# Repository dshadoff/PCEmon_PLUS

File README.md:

# PCEmon_PLUS

This project is meant to enhance Chris Covell's PCEmon, which can be found here:
https://chrismcovell.com/PCEmon/index.html

This board implements a microcontroller (Adafruit Feather M0 Adalogger), to
simplify some operations and to generally make life easier for the PCEmon user.
Software is written using the Arduino IDE.

I am hoping that others find this useful, and are able to contribute to the
project in order to add new functionality.  I am open to improving the hardware
in future, if it would be helpful for the functionality added.

Features:
- Instead of swapping cables between joypad and computer, this board can change
which input is active, with the touch of a pad on the microcontroller board
- Currently, it powers up with a shell pass-thru interface with the original
PCEmon commands; touching the 'PLUS mode' touchpad on the board will bring up
an alternate interface which is being built, but can currently view and scroll
through main memory and VRAM (with more to come)

NOTES:
------
Recommended Teraterm settings by Setup menu area:
Terminal:
- New-line: Transmit - change to LF

Font:
- If you use Teraterm on Windows, I found that the default font is thin and wispy; a better
  font to use is "HGSoeiKakuGothicUB" (Regular)

Serial Port:
- Start with default 19200

Additional Settings, 'General' tab:
- Unset "Clear display when window resized"
- Set "Display serial port speed"

TODOs:
------
- Add interactive memory edit
- Add ZMODEM transfers for easier data handling
- Add disassembler (and save to SDCard/computer)
- Add more clever management of input control (i.e. PCE can signal back with
extended /CLR=high signal, that PCE is ready for PCEmoninput)

This is prototype software, and as such has been minimally tested.
Use at your own risk.

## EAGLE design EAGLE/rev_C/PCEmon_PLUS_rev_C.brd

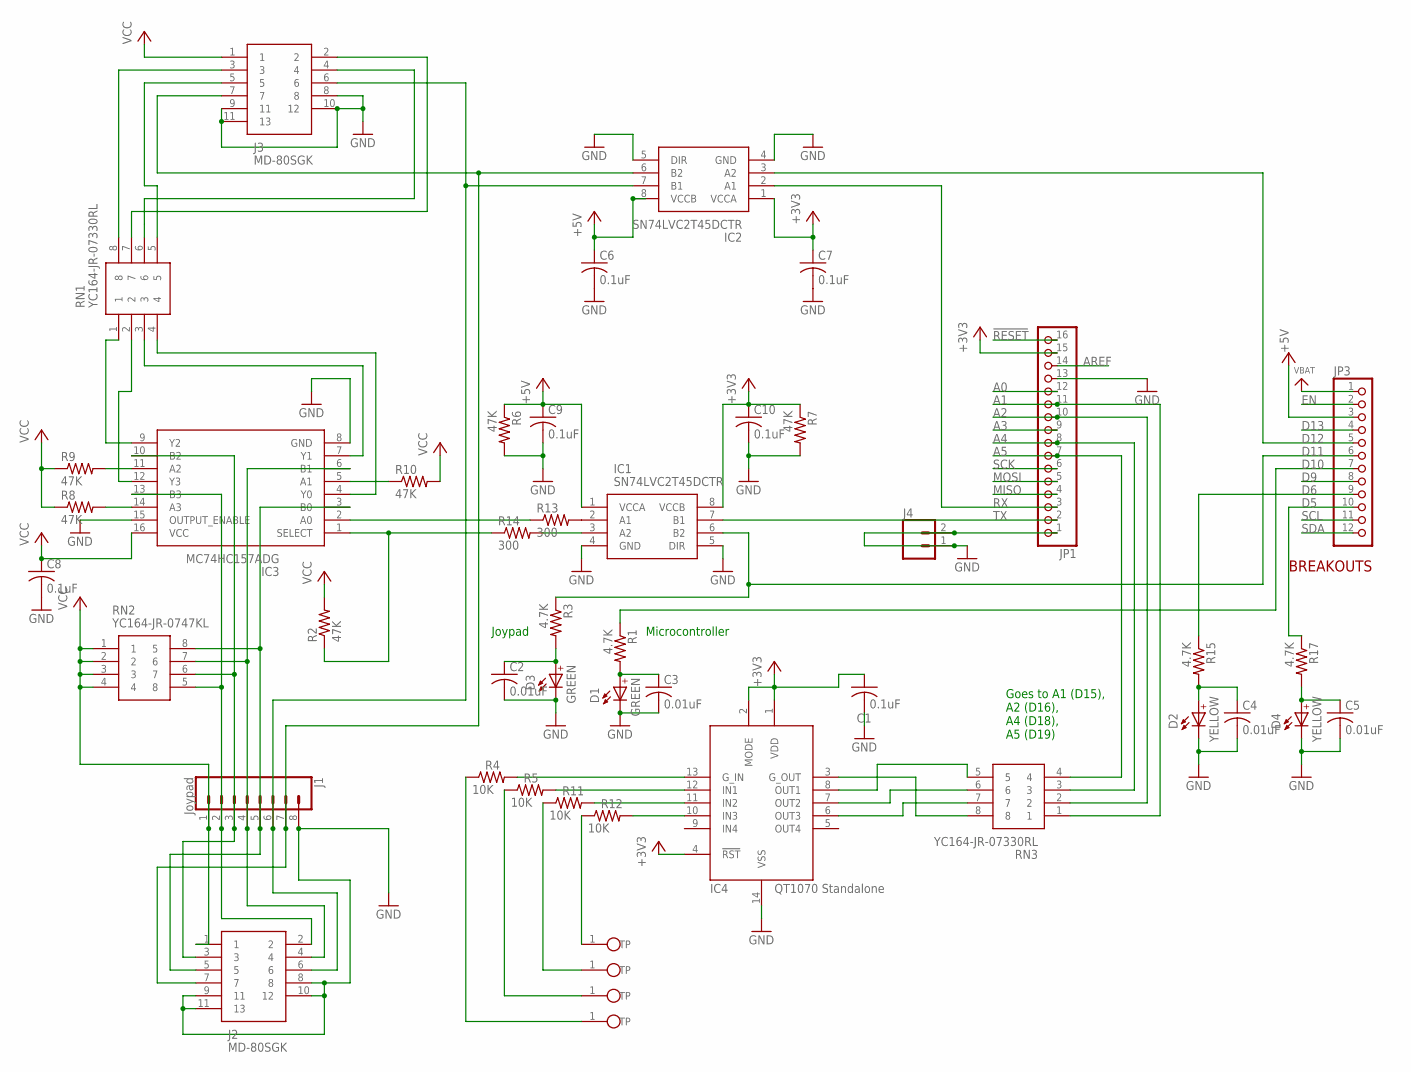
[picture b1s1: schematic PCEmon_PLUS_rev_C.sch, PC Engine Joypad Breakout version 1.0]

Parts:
C1, C6, C7, C8, C9, C10: 0.1uF; C0603
C2, C3, C4, C5: 0.01uF; C0603
D1, D3: GREEN; WL-SMCC_0603_R/Y/V
D2, D4: YELLOW; WL-SMCC_0603_R/Y/V
IC1, IC2: SN74LVC2T45DCTR; SOP65P400X130-8N
IC3: MC74HC157ADG; SOIC127P600X175-16N
IC4: AT42QT1070-SSU; SO14
J1: Joypad; 1X08
J2, J3: MD-80SGK; MD80SGK
J4: CONN_021X02_NO_SILK; 1X02_NO_SILK
JP1: HEADER-1X16ROUND; 1X16_ROUND
JP3: HEADER-1X12; 1X12_ROUND
P1: JOYPAD; TOUCH-350X500
P2: COMPUTER; TOUCH-350X500
P3: Original Mode; TOUCH-350X500
P4: PLUS Mode; TOUCH-350X500
R1, R3, R15, R17: 4.7K; R0603
R2, R6, R7, R8, R9, R10: 47K; R0603
R4, R5, R11, R12: 10K; R0603
R13, R14: 300; R0603
RN1, RN3: YC164-JR-07330RL; YC164JR07220RL
RN2: YC164-JR-0747KL; YC164JR07220RL

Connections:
!RESET: JP1.16
+3V3: C1.1, C7.1, C10.1, IC1.8 (VCCB), IC2.1 (VCCA), IC4.1 (VDD), IC4.2 (MODE), IC4.4 (!RST), JP1.15, R7.1
+5V: C6.1, C9.1, IC1.1 (VCCA), IC2.8 (VCCB), JP3.3, R6.1
A0: JP1.12
A1: JP1.11, RN3.1
A2: JP1.10, RN3.2
A3: JP1.9
A4: JP1.8, RN3.3
A5: JP1.7, RN3.4
AREF: JP1.14
D5: JP3.10, R17.1
D6: JP3.9, R15.1
D9: JP3.8
D10: JP3.7, R1.1
D11: IC1.6 (B2), JP3.6, R3.1
D12: IC2.3 (A2), JP3.5
D13: JP3.4
EN: JP3.2
GND: C1.2, C2.2, C3.2, C4.2, C5.2, C6.2, C7.2, C8.2, C9.2, C10.2, D1.1 (C), D2.1 (C), D3.1 (C), D4.1 (C), IC1.4 (GND), IC1.5 (DIR), IC2.4 (GND), IC2.5 (DIR), IC3.8 (GND), IC3.15 (OUTPUT_ENABLE), IC4.14 (VSS), J1.8, J2.8, J2.9 (11), J2.10 (12), J2.11 (13), J3.8, J3.9 (11), J3.10 (12), J3.11 (13), J4.1, J4.2, JP1.1, JP1.13, R6.2, R7.2
MISO: JP1.4
MOSI: JP1.5
unnamed: C2.1, D3.2 (A), R3.2
unnamed: IC3.10 (B2), J1.3, J2.3, RN2.6 (7)
unnamed: IC3.13 (B3), J1.2, J2.2, RN2.5 (8)
unnamed: IC3.6 (B1), J1.4, J2.4, RN2.7 (6)
unnamed: IC3.3 (B0), J1.5, J2.5, RN2.8 (5)
unnamed: IC2.7 (B1), J1.6, J2.6, J3.6
unnamed: IC2.6 (B2), J1.7, J2.7, J3.7
unnamed: J3.5, RN1.5
unnamed: C3.1, D1.2 (A), R1.2
unnamed: J3.4, RN1.6
unnamed: J3.3, RN1.8
unnamed: IC3.14 (A3), R8.2
unnamed: IC3.11 (A2), R9.2
unnamed: IC3.1 (SELECT), R2.1, R14.1
unnamed: IC1.2 (A1), R13.2
unnamed: IC3.5 (A1), R10.1
unnamed: IC3.9 (Y2), RN1.1
unnamed: IC3.2 (A0), R13.1
unnamed: IC1.3 (A2), R14.2
unnamed: IC3.12 (Y3), RN1.2
unnamed: IC4.13 (G_IN), R4.2
unnamed: IC3.4 (Y0), RN1.4
unnamed: J3.2, RN1.7
unnamed: IC3.7 (Y1), RN1.3
unnamed: IC4.12 (IN1), R5.2
unnamed: IC4.11 (IN2), R11.2
unnamed: IC4.10 (IN3), R12.2
unnamed: IC4.3 (G_OUT), RN3.8
unnamed: IC4.6 (OUT3), RN3.7
unnamed: IC4.7 (OUT2), RN3.6
unnamed: IC4.8 (OUT1), RN3.5
unnamed: P3.1, R5.1
unnamed: P4.1, R4.1
unnamed: P2.1, R11.1
unnamed: P1.1, R12.1
unnamed: C4.1, D2.2 (A), R15.2
unnamed: C5.1, D4.2 (A), R17.2
RX: IC2.2 (A1), JP1.3
SCK: JP1.6
SCL: JP3.11
SDA: JP3.12
TX: IC1.7 (B1), JP1.2
VBAT: JP3.1
VCC: C8.1, IC3.16 (VCC), J1.1, J2.1, J3.1, R2.2, R8.1, R9.1, R10.2, RN2.1, RN2.2, RN2.3, RN2.4

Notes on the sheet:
BREAKOUTS
Joypad
Microcontroller
Goes to A1 (D15), A2 (D16), A4 (D18), A5 (D19)

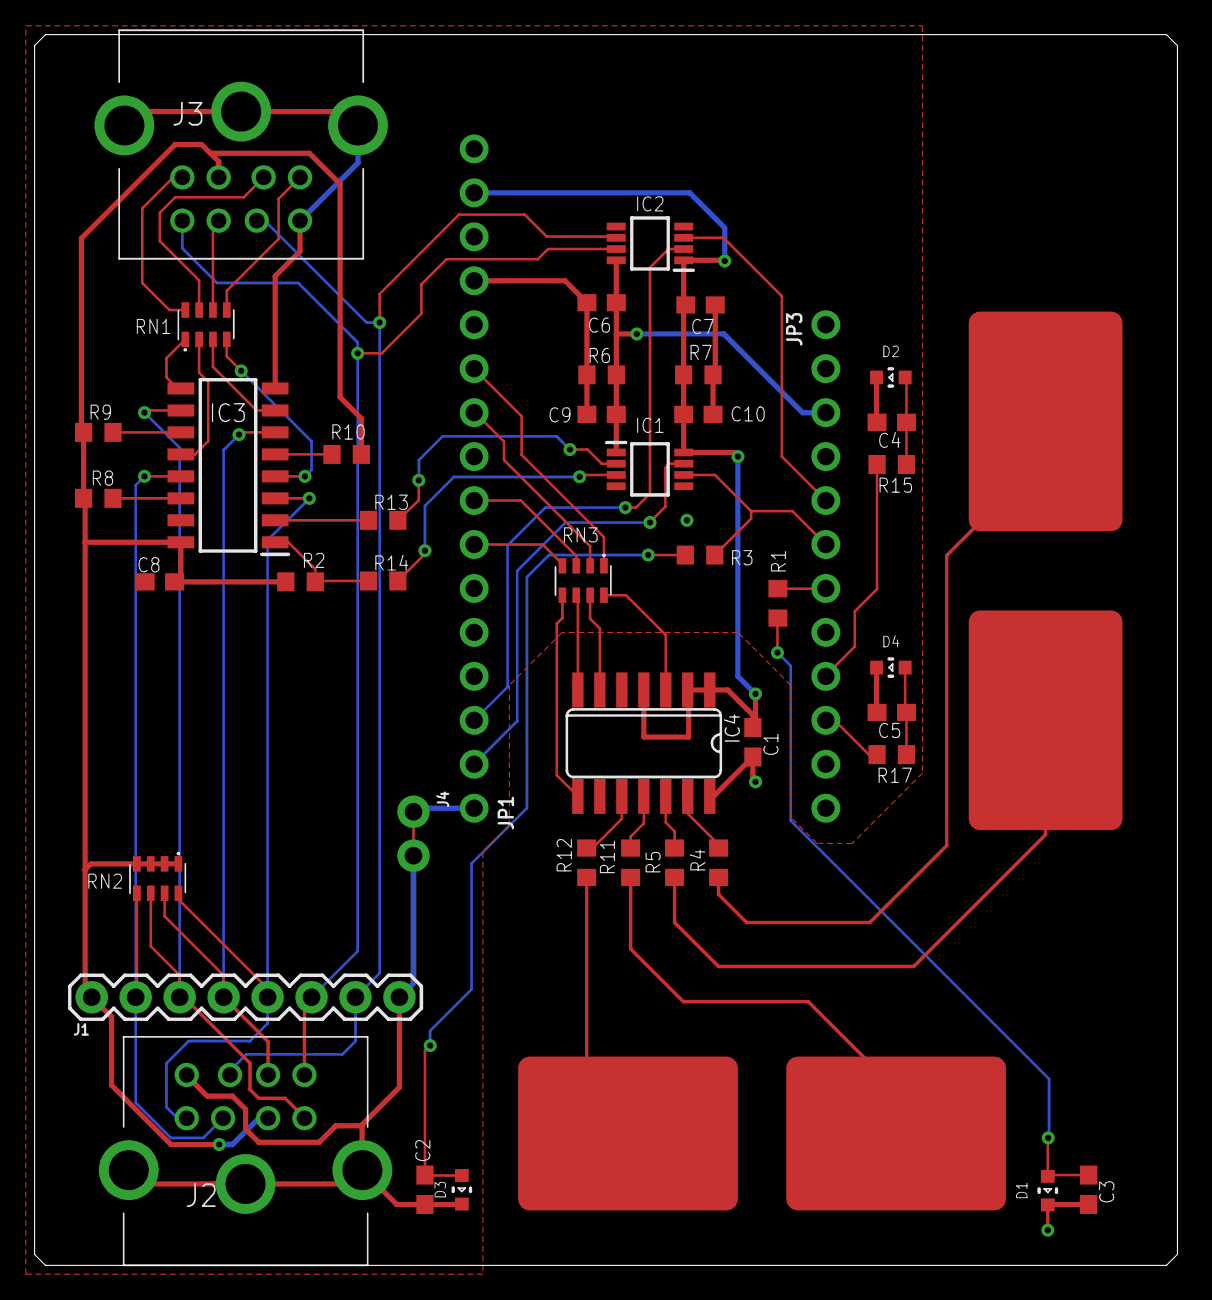
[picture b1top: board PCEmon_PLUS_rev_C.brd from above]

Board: 2 copper layers, 66.0 x 71.1 mm, 47 parts (0 on the bottom side), 52 nets.

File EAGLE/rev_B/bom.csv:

Qty,Designator,Footprint,Comment,LCSC Part # (optional),Description (optional)
5,"C6, C7, C8, C9, C10",C0603,100nF 50V X7R,C14663,MULTILAYER CERAMIC CAPACITORS MLCC - SMD/SMT 100NF 50V 0603 ROHS
6,"R13, R14, R15, R16, R17, R18",R0603,300Ω 1%,C23025,CHIP RESISTOR - SURFACE MOUNT 300OHMS ±1% 1/10W 0603 ROHS
2,"R1, R3",R0603,4.7KΩ 1%,C23162,CHIP RESISTOR - SURFACE MOUNT 4.7KOHMS ±1% 1/10W 0603 ROHS
10,"R2, R4, R5, R6, R7, R8, R9, R10, R11, R12",R0603,47KΩ 1%,C25819,CHIP RESISTOR - SURFACE MOUNT 47KOHMS ±1% 1/10W 0603 ROHS
2,"D1, D3",CHIP-LED0603,GREEN,C72043,LIGHT EMITTING DIODES (LED) GREEN 520~535NM 112~258MCD@20MA TOP VIEW 0603 ROHS
1,IC3,SOIC-16_3.9x9.9x1.27P,"74HC157D,653",C5609,74 SERIES MULTIPLEXERS 2V ~ 6V SOIC-16_150MIL ROHS
2,"IC1, IC2",SM-8_2.8x3.0x0.65P,SN74LVC2T45DCTR,C22672,74 SERIES 1 1.65V ~ 5.5V SM8 ROHS
1,J1,1x08_ROUND,pin header,Do not populate,
2,"J2, J3",MD80SGK,MD-80SGK,Do not populate,
1,JP3,1X12_ROUND,pin header,Do not populate,
1,JP1,1X16_ROUND,pin header,Do not populate,

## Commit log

2019-12-17 Added: - echo synchronization - 1-button BRAM backup - slightly clearer view of data direction (PCE versus Serial1)
2019-12-20 Add Rev. B boards into repo bom.csv and assembly.csv were files needed by JLCPCB SMT assembly
2019-12-29 Add more framework; communications and memory view/scroll now working
2019-12-31 Various bug fixes & improvements; improve help text and give some color
2020-01-06 - added flag display, VRAM display - started implementing commands ("View" in this case) - various minor fixes and improvements
2020-01-06 - update REVISIONS.md file
2020-01-18 add 'Address' command, 1-byte scroll movements; fix bugs, adjust formatting
2020-01-18 fix date on REVISIONS.md comment
2020-02-22 Add new 'rev. C' board design,
    Add new 'rev. C' board design with touch sensros to switch inputs and monitor modes
2020-02-23 Update to Rev. C boards
    - update boards to revision C
    - adjust code to make use of touchpads instead of key commands to switch inputs or operating modes
    - add recommended Teraterm settings
2020-03-18 Performance improvement
    Reduce chance of USB packet overflow at PC side, by increasing payload size and reducing frequency to 250 per second.
2020-06-06 Fix register alignment
    Fix register alignment

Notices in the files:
EAGLE/rev_C/PCEmon_PLUS_rev_C.brd:
(C)2020 David Shadoff
parts and their libraries:
SparkFun-Connectors: Licensing: Creative Commons ShareAlike 4.0 International - https://creativecommons.org/licenses/by-sa/4.0
microbuilder: This work is placed in the public domain, and may be freely used for commercial and non-commercial work with the following conditions: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
